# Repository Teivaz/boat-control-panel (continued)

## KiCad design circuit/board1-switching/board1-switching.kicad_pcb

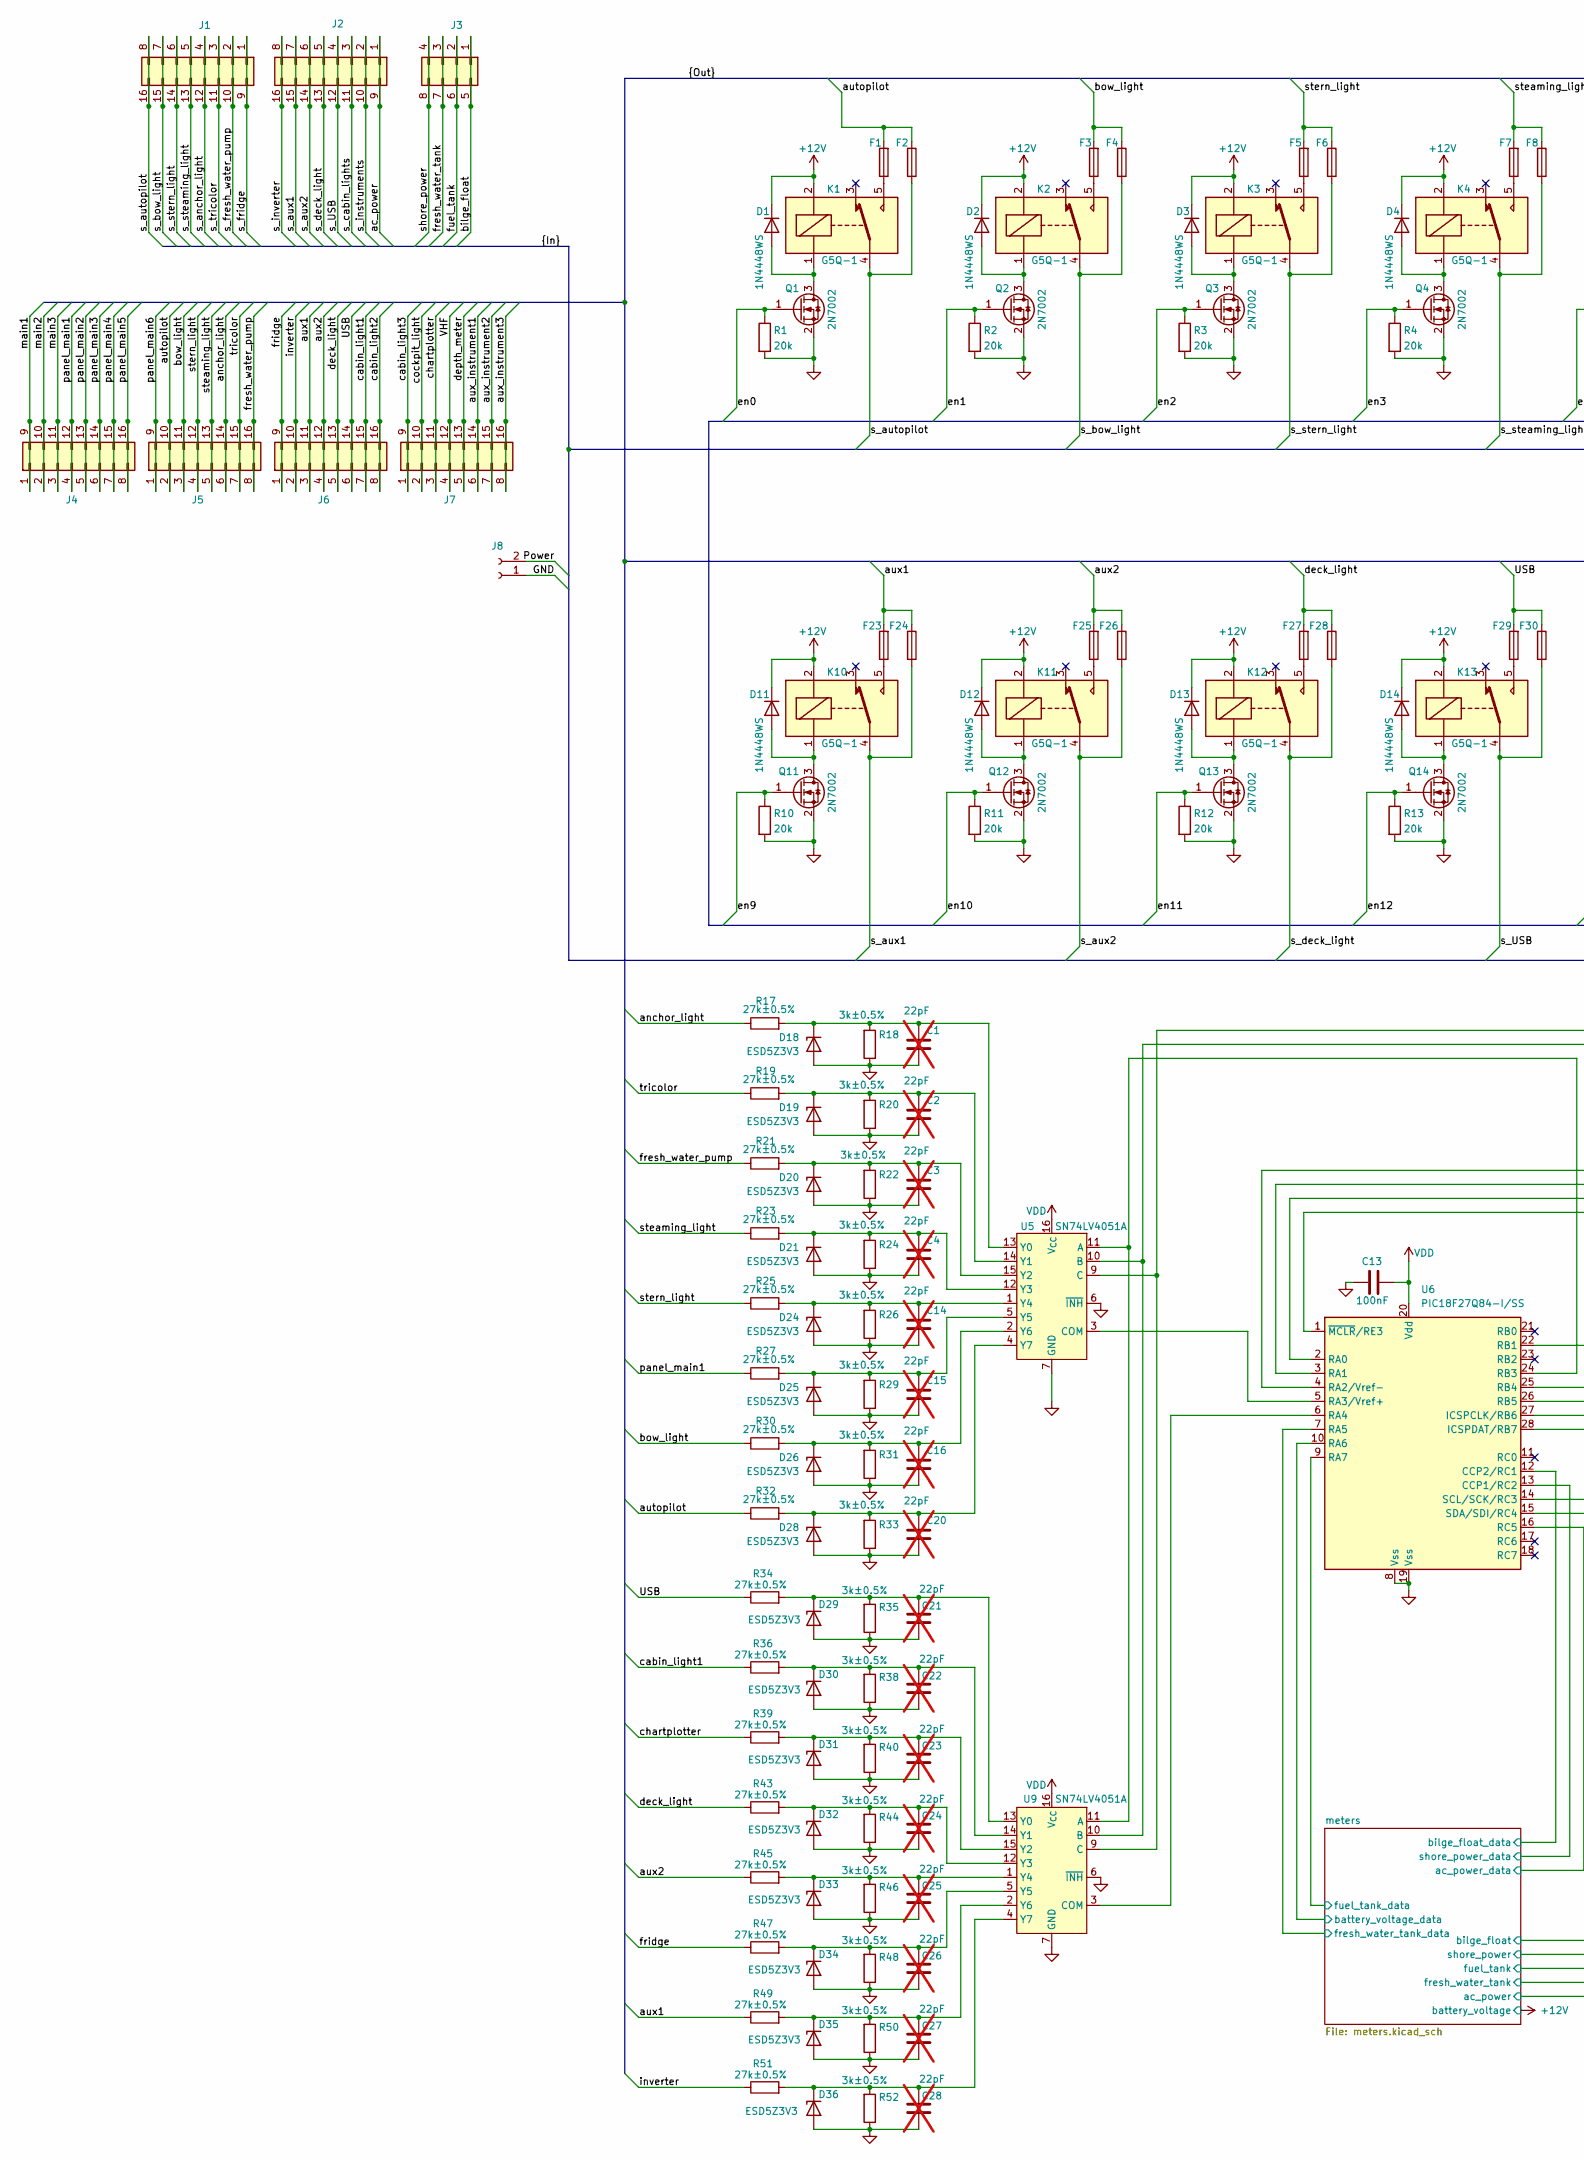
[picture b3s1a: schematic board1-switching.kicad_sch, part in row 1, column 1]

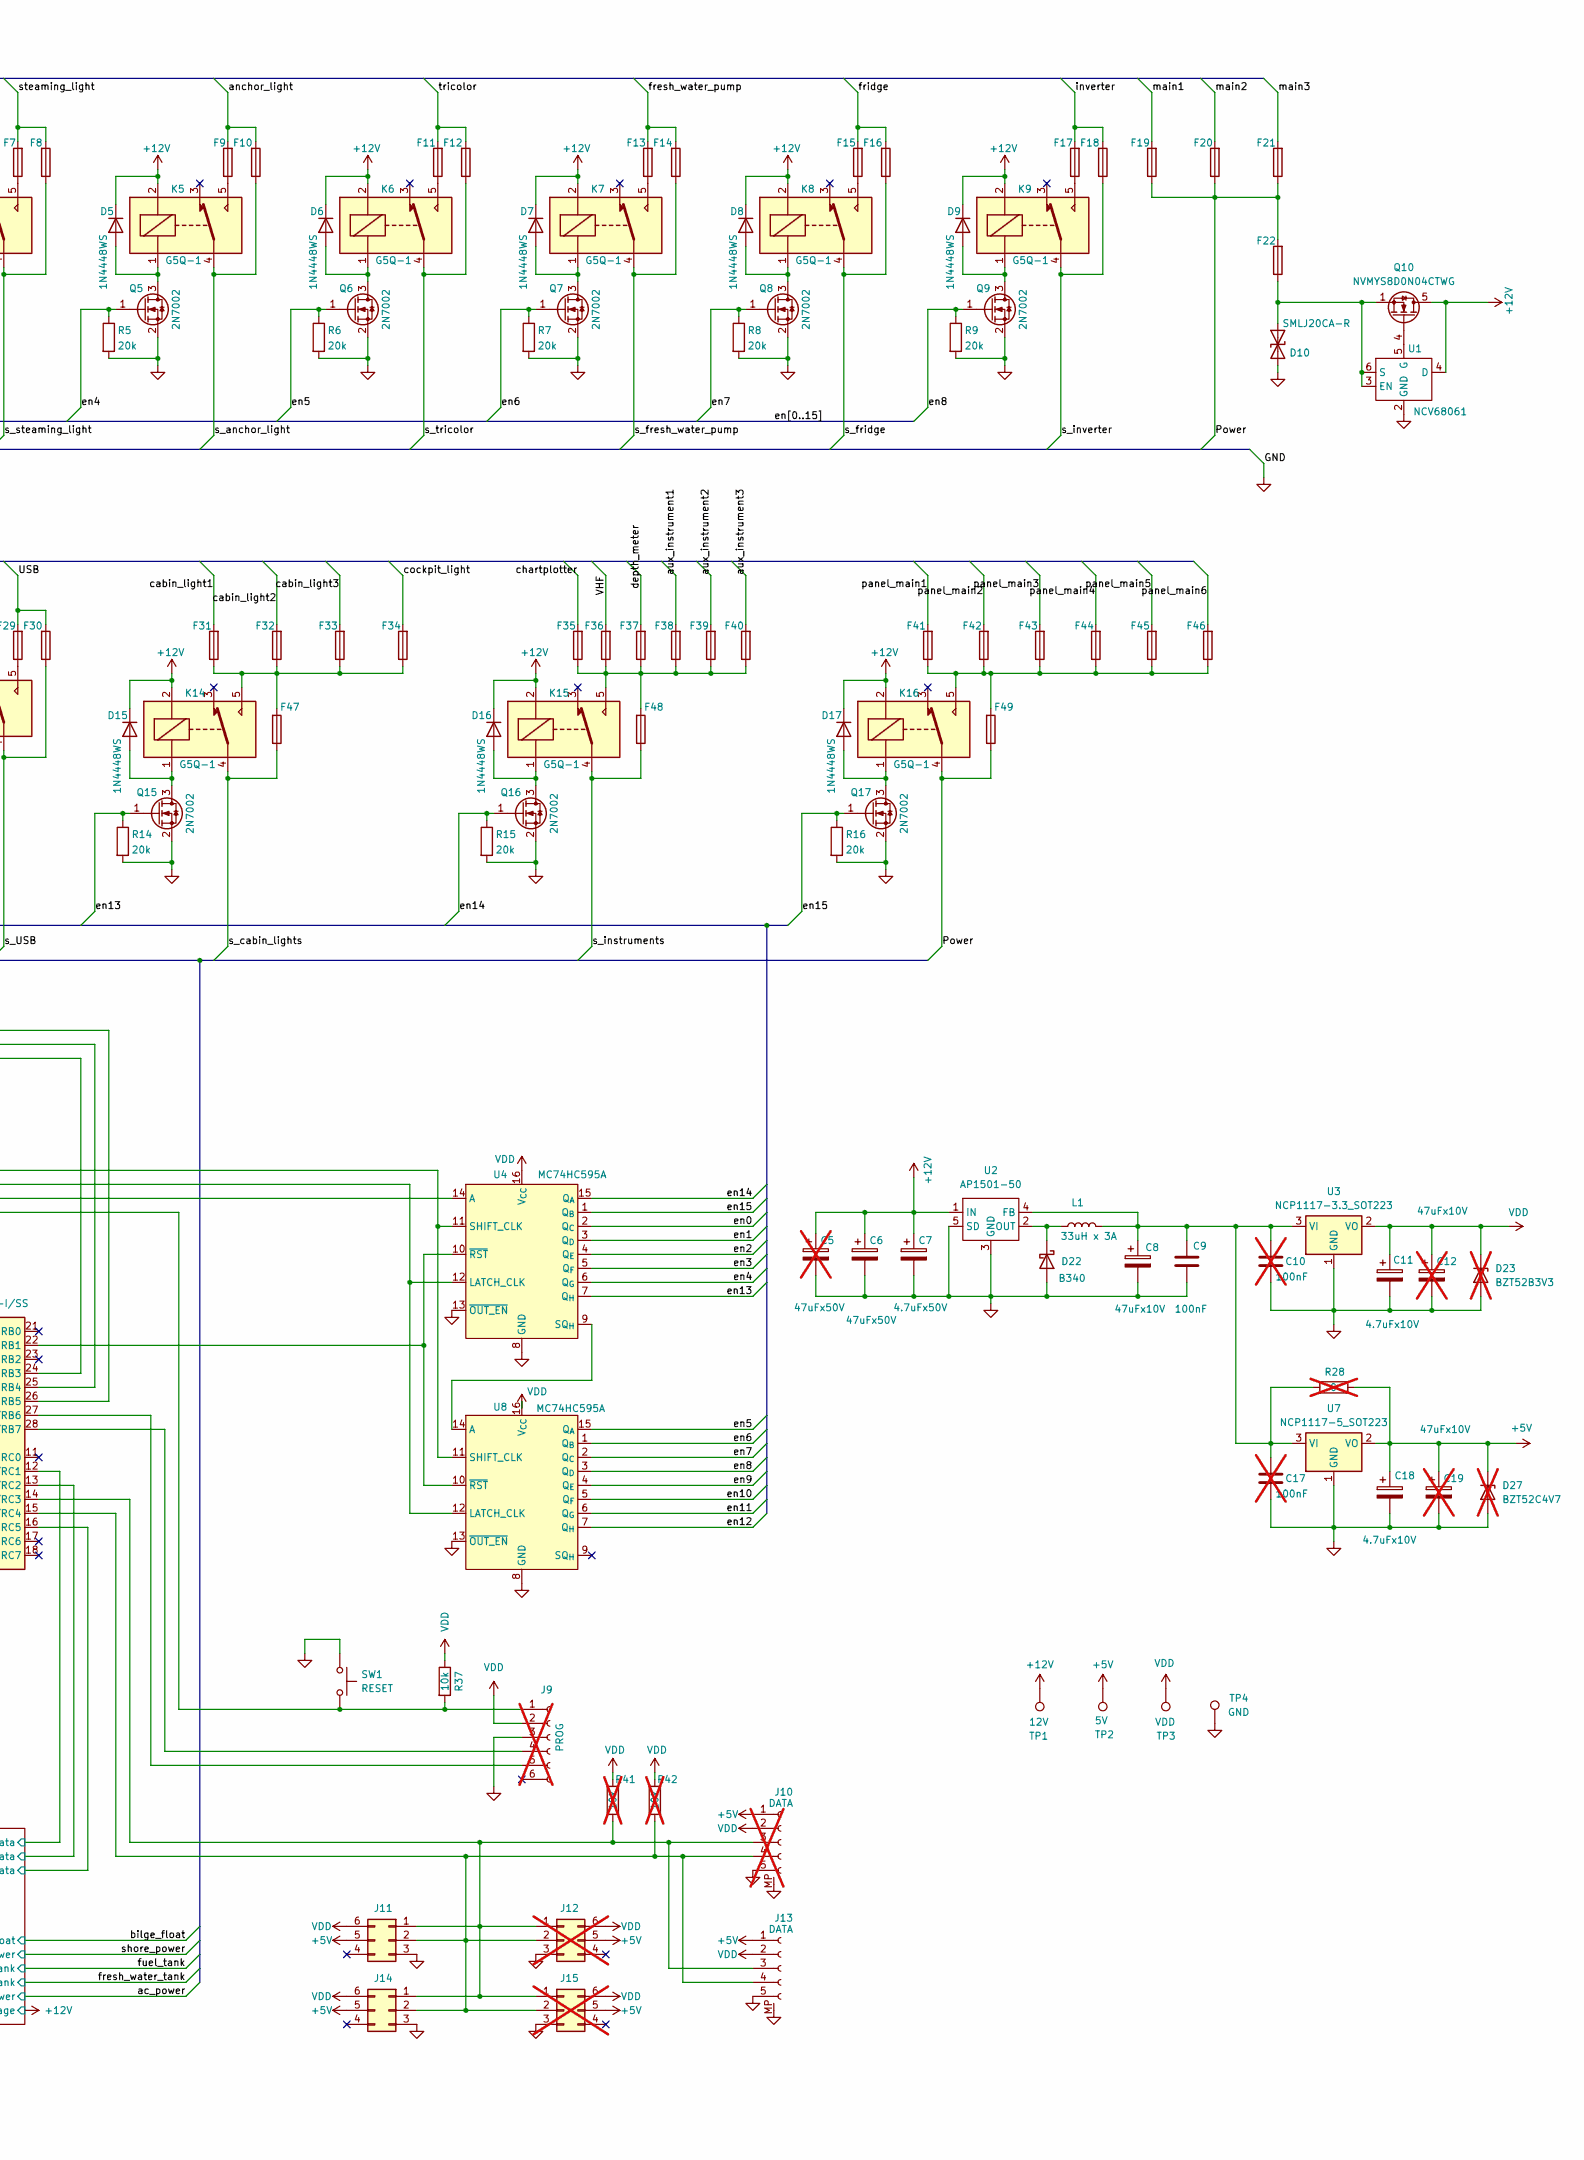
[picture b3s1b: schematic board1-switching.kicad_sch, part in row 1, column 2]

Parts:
C1, C2, C3, C4, C14, C15, C16, C20, C21, C22, C23, C24, C25, C26, C27, C28: 22pF; C_0805_2012Metric_Pad1.18x1.45mm_HandSolder; not fitted
C5: 47uFx50V; CP_Elec_8x6.5; not fitted
C6: 47uFx50V; CP_Elec_8x6.5
C7: 4.7uFx50V; C_Elec_5x5.4
C8: 47uFx10V; CP_EIA-3528-12_Kemet-T_HandSolder
C9, C13: 100nF; C_0805_2012Metric_Pad1.18x1.45mm_HandSolder
C10, C17: 100nF; C_0805_2012Metric_Pad1.18x1.45mm_HandSolder; not fitted
C11, C18: 4.7uFx10V; CP_EIA-3216-10_Kemet-I_HandSolder
C12, C19: 47uFx10V; CP_EIA-3528-12_Kemet-T_HandSolder; not fitted
D1, D2, D3, D4, D5, D6, D7, D8, D9, D11, D12, D13, D14, D15, D16, D17: 1N4448WS; D_SOD-323_HandSoldering
D10: SMLJ20CA-R; D_SMC
D18, D19, D20, D21, D24, D25, D26, D28, D29, D30, D31, D32, D33, D34, D35, D36: ESD5Z3V3; D_SOD-523
D22: B340; D_B340-SMAF
D23: BZT52B3V3; D_SOD-123F; not fitted
D27: BZT52C4V7; D_SOD-123F; not fitted
F1, F2, F3, F4, F5, F6, F7, F8, F9, F10, F11, F12, F13, F14, F15, F16, F17, F18, F19, F20, F21, F22, F23, F24, F25, F26, F27, F28, F29, F30, F31, F32, F33, F34, F35, F36, F37, F38, F39, F40, F41, F42, F43, F44, F45, F46, F47, F48, F49: Fuse-Keystone-3557-2
J1, J2, J4, J5, J6, J7: Con_2x08_Amphenol-QT08CDP
J3: Con_2x04_Amphenol-QT04CDP
J8: J_Molex_38710-6302
J9: PinHeader_1x06_P2.54mm_Vertical; not fitted
J10: Molex_Pico-Lock_504050-0591_1x05-1MP_P1.50mm_Horizontal; not fitted
J11, J14: Conn_02x03_Counter_Clockwise; Con-Amphenol-76385-303LF
J12, J15: Conn_02x03_Counter_Clockwise; Con-Amphenol-76385-303LF; not fitted
J13: Molex_Pico-Lock_504050-0591_1x05-1MP_P1.50mm_Horizontal
K1, K2, K3, K4, K5, K6, K7, K8, K9, K10, K11, K12, K13, K14, K15, K16: G5Q-1; Relay-TE-V23086-C1xxx
L1: 33uH x 3A; L_Abracon_AMDLA1004S-330MT
Q1, Q2, Q3, Q4, Q5, Q6, Q7, Q8, Q9, Q11, Q12, Q13, Q14, Q15, Q16, Q17: 2N7002; SOT-23
Q10: NVMYS8D0N04CTWG; LFPAK4_4.90x4.15x1.15MM_1.27P
R1, R2, R3, R4, R5, R6, R7, R8, R9, R10, R11, R12, R13, R14, R15, R16: 20k; R_0805_2012Metric_Pad1.20x1.40mm_HandSolder
R17, R19, R21, R23, R25, R27, R30, R32, R34, R36, R39, R43, R45, R47, R49, R51: 27k±0.5%; R_0805_2012Metric_Pad1.20x1.40mm_HandSolder
R18, R20, R22, R24, R26, R29, R31, R33, R35, R38, R40, R44, R46, R48, R50, R52: 3k±0.5%; R_0805_2012Metric_Pad1.20x1.40mm_HandSolder
R28: 0; R_0805_2012Metric_Pad1.20x1.40mm_HandSolder; not fitted
R37: 10k; R_0805_2012Metric_Pad1.20x1.40mm_HandSolder
R41, R42: 10k; R_0805_2012Metric_Pad1.20x1.40mm_HandSolder; not fitted
SW1: RESET; ButtonSMT_CnK_KSC2_J
TP1: 12V; TestPoint_Pad_D2.0mm
TP2: 5V; TestPoint_Pad_D2.0mm
TP3: VDD; TestPoint_Pad_D2.0mm
TP4: GND; TestPoint_Pad_D2.0mm
U1: NCV68061; TSOP-6_3.00x1.5x0.90mm_P0.95mm
U2: AP1501-50; TO-263-5_TabPin3
U3: NCP1117-3.3_SOT223; SOT-223-3_TabPin2
U4, U8: MC74HC595A; SOIC-16_3.9x9.9mm_P1.27mm
U5, U9: SN74LV4051A; SOIC-16_3.9x9.9mm_P1.27mm
U6: PIC18F27Q84-I/SS; SSOP-28-5.3mm
U7: NCP1117-5_SOT223; SOT-223-3_TabPin2

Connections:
+5V: C18.1, C19.1, D27.1 (K), J10.1, J11.5, J12.5, J13.1, J14.5, J15.5, R28.1, TP2.1, U7.2 (VO); also elsewhere on the board
+12V: C5.1, C6.1, C7.1, D1.1 (K), D2.1 (K), D3.1 (K), D4.1 (K), D5.1 (K), D6.1 (K), D7.1 (K), D8.1 (K), D9.1 (K), D11.1 (K), D12.1 (K), D13.1 (K), D14.1 (K), D15.1 (K), D16.1 (K), D17.1 (K), K1.2, K2.2, K3.2, K4.2, K5.2, K6.2, K7.2, K8.2, K9.2, K10.2, K11.2, K12.2, K13.2, K14.2, K15.2, K16.2, Q10.5 (D), TP1.1, U1.4 (D), U2.1 (IN); also elsewhere on the board
/Power: F19.1, F19.2, F20.1, F20.2, F21.1, F21.2, F22.3, F22.4, F49.1, F49.2, J8.2, K16.4
/USB: F29.3, F29.4, F30.3, F30.4, J6.6, J6.14, R34.1
/VHF: F36.3, F36.4, J7.4, J7.12
/ac_power: J2.1, J2.9; also elsewhere on the board
/anchor_light: F9.3, F9.4, F10.3, F10.4, J5.6, J5.14, R17.1
/autopilot: F1.3, F1.4, F2.3, F2.4, J5.2, J5.10, R32.1
/aux1: F23.3, F23.4, F24.3, F24.4, J6.3, J6.11, R49.1
/aux2: F25.3, F25.4, F26.3, F26.4, J6.4, J6.12, R45.1
/aux_instrument1: F38.3, F38.4, J7.6, J7.14
/aux_instrument2: F39.3, F39.4, J7.7, J7.15
/aux_instrument3: F40.3, F40.4, J7.8, J7.16
/bilge_float: J3.1, J3.5; also elsewhere on the board
/bow_light: F3.3, F3.4, F4.3, F4.4, J5.3, J5.11, R30.1
/cabin_light1: F31.3, F31.4, J6.7, J6.15, R36.1
/cabin_light2: F32.3, F32.4, J6.8, J6.16
/cabin_light3: F33.3, F33.4, J7.1, J7.9
/chartplotter: F35.3, F35.4, J7.3, J7.11, R39.1
/cockpit_light: F34.3, F34.4, J7.2, J7.10
/deck_light: F27.3, F27.4, F28.3, F28.4, J6.5, J6.13, R43.1
/depth_meter: F37.3, F37.4, J7.5, J7.13
/en0: Q1.1 (G), R1.1, U4.2 (Q_{C})
/en1: Q2.1 (G), R2.1, U4.3 (Q_{D})
/en2: Q3.1 (G), R3.1, U4.4 (Q_{E})
/en3: Q4.1 (G), R4.1, U4.5 (Q_{F})
/en4: Q5.1 (G), R5.1, U4.6 (Q_{G})
/en5: Q6.1 (G), R6.1, U8.15 (Q_{A})
/en6: Q7.1 (G), R7.1, U8.1 (Q_{B})
/en7: Q8.1 (G), R8.1, U8.2 (Q_{C})
/en8: Q9.1 (G), R9.1, U8.3 (Q_{D})
/en9: Q11.1 (G), R10.1, U8.4 (Q_{E})
/en10: Q12.1 (G), R11.1, U8.5 (Q_{F})
/en11: Q13.1 (G), R12.1, U8.6 (Q_{G})
/en12: Q14.1 (G), R13.1, U8.7 (Q_{H})
/en13: Q15.1 (G), R14.1, U4.7 (Q_{H})
/en14: Q16.1 (G), R15.1, U4.15 (Q_{A})
/en15: Q17.1 (G), R16.1, U4.1 (Q_{B})
/fresh_water_pump: F13.3, F13.4, F14.3, F14.4, J5.8, J5.16, R21.1
/fresh_water_tank: J3.3, J3.7; also elsewhere on the board
/fridge: F15.3, F15.4, F16.3, F16.4, J6.1, J6.9, R47.1
/fuel_tank: J3.2, J3.6; also elsewhere on the board
/inverter: F17.3, F17.4, F18.3, F18.4, J6.2, J6.10, R51.1
/main1: F19.3, F19.4, J4.1, J4.9
/main2: F20.3, F20.4, J4.2, J4.10
/main3: F21.3, F21.4, J4.3, J4.11
/meters/ac_power_data: U6.16 (RC5); also elsewhere on the board
/meters/battery_voltage_data: U6.10 (RA6); also elsewhere on the board
/meters/bilge_float_data: U6.12 (CCP2/RC1); also elsewhere on the board
/meters/fresh_water_tank_data: U6.7 (RA5); also elsewhere on the board
/meters/fuel_tank_data: U6.9 (RA7); also elsewhere on the board
/meters/shore_power_data: U6.13 (CCP1/RC2); also elsewhere on the board
/panel_main1: F41.3, F41.4, J4.4, J4.12, R27.1
/panel_main2: F42.3, F42.4, J4.5, J4.13
/panel_main3: F43.3, F43.4, J4.6, J4.14
/panel_main4: F44.3, F44.4, J4.7, J4.15
/panel_main5: F45.3, F45.4, J4.8, J4.16
/panel_main6: F46.3, F46.4, J5.1, J5.9
/s_USB: F30.1, F30.2, J2.4, J2.12, K13.4
/s_anchor_light: F10.1, F10.2, J1.4, J1.12, K5.4
/s_autopilot: F2.1, F2.2, J1.8, J1.16, K1.4
/s_aux1: F24.1, F24.2, J2.7, J2.15, K10.4
/s_aux2: F26.1, F26.2, J2.6, J2.14, K11.4
/s_bow_light: F4.1, F4.2, J1.7, J1.15, K2.4
/s_cabin_lights: F47.1, F47.2, J2.3, J2.11, K14.4
/s_deck_light: F28.1, F28.2, J2.5, J2.13, K12.4
/s_fresh_water_pump: F14.1, F14.2, J1.2, J1.10, K7.4
/s_fridge: F16.1, F16.2, J1.1, J1.9, K8.4
/s_instruments: F48.1, F48.2, J2.2, J2.10, K15.4
/s_inverter: F18.1, F18.2, J2.8, J2.16, K9.4
/s_steaming_light: F8.1, F8.2, J1.5, J1.13, K4.4
/s_stern_light: F6.1, F6.2, J1.6, J1.14, K3.4
/s_tricolor: F12.1, F12.2, J1.3, J1.11, K6.4
/shore_power: J3.4, J3.8; also elsewhere on the board
/steaming_light: F7.3, F7.4, F8.3, F8.4, J5.5, J5.13, R23.1
/stern_light: F5.3, F5.4, F6.3, F6.4, J5.4, J5.12, R25.1
/tricolor: F11.3, F11.4, F12.3, F12.4, J5.7, J5.15, R19.1
GND: C1.1, C2.1, C3.1, C4.1, C5.2, C6.2, C7.2, C8.2, C9.2, C10.2, C11.2, C12.2, C13.2, C14.1, C15.1, C16.1, C17.2, C18.2, C19.2, C20.1, C21.1, C22.1, C23.1, C24.1, C25.1, C26.1, C27.1, C28.1, D10.2 (A2), D18.2 (A), D19.2 (A), D20.2 (A), D21.2 (A), D22.2 (A), D23.2 (A), D24.2 (A), D25.2 (A), D26.2 (A), D27.2 (A), D28.2 (A), D29.2 (A), D30.2 (A), D31.2 (A), D32.2 (A), D33.2 (A), D34.2 (A), D35.2 (A), D36.2 (A), J8.1, J9.3, J10.5, J10.MP, J11.3, J12.3, J13.5, J13.MP, J14.3, J15.3, Q1.2 (S), Q2.2 (S), Q3.2 (S), Q4.2 (S), Q5.2 (S), Q6.2 (S), Q7.2 (S), Q8.2 (S), Q9.2 (S), Q11.2 (S), Q12.2 (S), Q13.2 (S), Q14.2 (S), Q15.2 (S), Q16.2 (S), Q17.2 (S), R1.2, R2.2, R3.2, R4.2, R5.2, R6.2, R7.2, R8.2, R9.2, R10.2, R11.2, R12.2, R13.2, R14.2, R15.2, R16.2, R18.1, R20.1, R22.1, R24.1, R26.1, R29.1, R31.1, R33.1, R35.1, R38.1, R40.1, R44.1, R46.1, R48.1, R50.1, R52.1, SW1.1, SW1.3, TP4.1, U1.2 (GND), U2.3 (GND), U2.5 (SD), U3.1 (GND), U4.8 (GND), U4.13 (~OUT_EN), U5.6 (~INH), U5.7 (GND), U5.8 (GND), U6.8 (Vss), U6.19 (Vss), U7.1 (GND), U8.8 (GND), U8.13 (~OUT_EN), U9.6 (~INH), U9.7 (GND), U9.8 (GND); also elsewhere on the board
unnamed: D1.2 (A), K1.1, Q1.3 (D)
unnamed: D2.2 (A), K2.1, Q2.3 (D)
unnamed: D3.2 (A), K3.1, Q3.3 (D)
unnamed: D4.2 (A), K4.1, Q4.3 (D)
unnamed: D5.2 (A), K5.1, Q5.3 (D)
unnamed: D6.2 (A), K6.1, Q6.3 (D)
unnamed: D7.2 (A), K7.1, Q7.3 (D)
unnamed: D8.2 (A), K8.1, Q8.3 (D)
unnamed: D9.2 (A), K9.1, Q9.3 (D)
unnamed: D10.1 (A1), F22.1, F22.2, Q10.1 (S), Q10.2 (S), Q10.3 (S), U1.3 (EN), U1.6 (S)
unnamed: D11.2 (A), K10.1, Q11.3 (D)
unnamed: D12.2 (A), K11.1, Q12.3 (D)
unnamed: D13.2 (A), K12.1, Q13.3 (D)
unnamed: D14.2 (A), K13.1, Q14.3 (D)
unnamed: D15.2 (A), K14.1, Q15.3 (D)
unnamed: D16.2 (A), K15.1, Q16.3 (D)
unnamed: D17.2 (A), K16.1, Q17.3 (D)
unnamed: C1.2, D18.1 (K), R17.2, R18.2, U5.13 (Y0)
unnamed: C2.2, D19.1 (K), R19.2, R20.2, U5.14 (Y1)
unnamed: C3.2, D20.1 (K), R21.2, R22.2, U5.15 (Y2)
unnamed: C4.2, D21.1 (K), R23.2, R24.2, U5.12 (Y3)
unnamed: D22.1 (K), L1.1, U2.2 (OUT)
unnamed: C14.2, D24.1 (K), R25.2, R26.2, U5.1 (Y4)
unnamed: C15.2, D25.1 (K), R27.2, R29.2, U5.5 (Y5)
unnamed: C16.2, D26.1 (K), R30.2, R31.2, U5.2 (Y6)
unnamed: C20.2, D28.1 (K), R32.2, R33.2, U5.4 (Y7)
unnamed: C21.2, D29.1 (K), R34.2, R35.2, U9.13 (Y0)
unnamed: C22.2, D30.1 (K), R36.2, R38.2, U9.14 (Y1)
unnamed: C23.2, D31.1 (K), R39.2, R40.2, U9.15 (Y2)
unnamed: C24.2, D32.1 (K), R43.2, R44.2, U9.12 (Y3)
unnamed: C25.2, D33.1 (K), R45.2, R46.2, U9.1 (Y4)
unnamed: C26.2, D34.1 (K), R47.2, R48.2, U9.5 (Y5)
unnamed: C27.2, D35.1 (K), R49.2, R50.2, U9.2 (Y6)
unnamed: C28.2, D36.1 (K), R51.2, R52.2, U9.4 (Y7)
unnamed: F1.1, F1.2, K1.5
unnamed: F3.1, F3.2, K2.5
unnamed: F5.1, F5.2, K3.5
unnamed: F7.1, F7.2, K4.5
unnamed: F9.1, F9.2, K5.5
unnamed: F11.1, F11.2, K6.5
unnamed: F13.1, F13.2, K7.5
unnamed: F15.1, F15.2, K8.5
unnamed: F17.1, F17.2, K9.5
unnamed: F23.1, F23.2, K10.5
unnamed: F25.1, F25.2, K11.5
unnamed: F27.1, F27.2, K12.5
unnamed: F29.1, F29.2, K13.5
unnamed: F31.1, F31.2, F32.1, F32.2, F33.1, F33.2, F34.1, F34.2, F47.3, F47.4, K14.5
unnamed: F35.1, F35.2, F36.1, F36.2, F37.1, F37.2, F38.1, F38.2, F39.1, F39.2, F40.1, F40.2, F48.3, F48.4, K15.5
unnamed: F41.1, F41.2, F42.1, F42.2, F43.1, F43.2, F44.1, F44.2, F45.1, F45.2, F46.1, F46.2, F49.3, F49.4, K16.5
unnamed: J9.1, R37.2, SW1.2, SW1.4, U6.1 (~MCLR/RE3)
unnamed: J9.4, U6.28 (ICSPDAT/RB7)
unnamed: J9.5, U6.27 (ICSPCLK/RB6)
unnamed: J10.3, J11.1, J12.1, J13.3, J14.1, J15.1, R41.2, U6.14 (SCL/SCK/RC3)
unnamed: J10.4, J11.2, J12.2, J13.4, J14.2, J15.2, R42.2, U6.15 (SDA/SDI/RC4)
unnamed: Q10.4 (G), U1.5 (G)
unnamed: C8.1, C9.1, C10.1, C17.1, L1.2, R28.2, U2.4 (FB), U3.3 (VI), U7.3 (VI)
unnamed: U4.14 (A), U6.2 (RA0)
unnamed: U4.12 (LATCH_CLK), U6.3 (RA1), U8.12 (LATCH_CLK)
unnamed: U4.11 (SHIFT_CLK), U6.4 (RA2/Vref-), U8.11 (SHIFT_CLK)
unnamed: U4.9 (SQ_{H}), U8.14 (A)
unnamed: U4.10 (~RST), U6.22 (RB1), U8.10 (~RST)
unnamed: U5.11 (A), U6.24 (RB3), U9.11 (A)
unnamed: U5.10 (B), U6.25 (RB4), U9.10 (B)
unnamed: U5.9 (C), U6.26 (RB5), U9.9 (C)
unnamed: U5.3 (COM), U6.5 (RA3/Vref+)
unnamed: U6.6 (RA4), U9.3 (COM)
VDD: C11.1, C12.1, C13.1, D23.1 (K), J9.2, J10.2, J11.6, J12.6, J13.2, J14.6, J15.6, R37.1, R41.1, R42.1, TP3.1, U3.2 (VO), U4.16 (V_{CC}), U5.16 (V_{CC}), U6.20 (Vdd), U8.16 (V_{CC}), U9.16 (V_{CC}); also elsewhere on the board

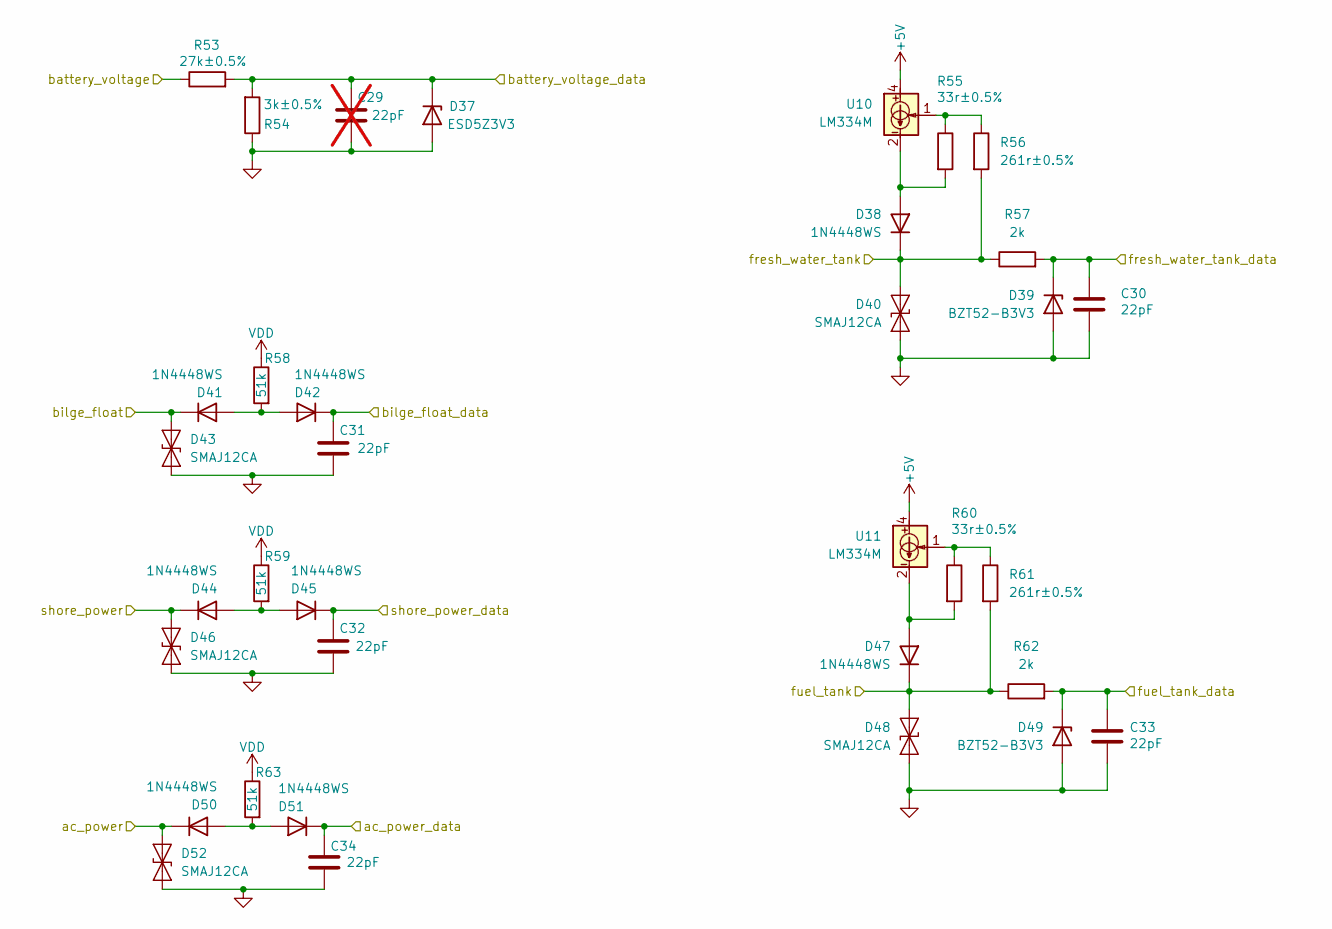
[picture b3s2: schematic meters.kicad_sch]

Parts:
C29: 22pF; C_0805_2012Metric_Pad1.18x1.45mm_HandSolder; not fitted
C30, C31, C32, C33, C34: 22pF; C_0805_2012Metric_Pad1.18x1.45mm_HandSolder
D37: ESD5Z3V3; D_SOD-523
D38, D41, D42, D44, D45, D47, D50, D51: 1N4448WS; D_SOD-323_HandSoldering
D39, D49: BZT52-B3V3; D_SOD-123
D40, D43, D46, D48, D52: SMAJ12CA; D_SMA
R53: 27k±0.5%; R_0805_2012Metric_Pad1.20x1.40mm_HandSolder
R54: 3k±0.5%; R_0805_2012Metric_Pad1.20x1.40mm_HandSolder
R55, R60: 33r±0.5%; R_0805_2012Metric_Pad1.20x1.40mm_HandSolder
R56, R61: 261r±0.5%; R_0805_2012Metric_Pad1.20x1.40mm_HandSolder
R57, R62: 2k; R_0805_2012Metric_Pad1.20x1.40mm_HandSolder
R58, R59, R63: 51k; R_0805_2012Metric_Pad1.20x1.40mm_HandSolder
U10, U11: LM334M; SOIC-8_3.9x4.9mm_P1.27mm

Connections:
+5V: U10.4, U11.4; also elsewhere on the board
+12V: R53.1; also elsewhere on the board
/ac_power: D50.1 (K), D52.2 (A2); also elsewhere on the board
/bilge_float: D41.1 (K), D43.2 (A2); also elsewhere on the board
/fresh_water_tank: D38.1 (K), D40.2 (A2), R56.2, R57.1; also elsewhere on the board
/fuel_tank: D47.1 (K), D48.2 (A2), R61.2, R62.1; also elsewhere on the board
/meters/ac_power_data: C34.1, D51.1 (K); also elsewhere on the board
/meters/battery_voltage_data: C29.2, D37.1 (K), R53.2, R54.2; also elsewhere on the board
/meters/bilge_float_data: C31.1, D42.1 (K); also elsewhere on the board
/meters/fresh_water_tank_data: C30.1, D39.1 (K), R57.2; also elsewhere on the board
/meters/fuel_tank_data: C33.1, D49.1 (K), R62.2; also elsewhere on the board
/meters/shore_power_data: C32.1, D45.1 (K); also elsewhere on the board
/shore_power: D44.1 (K), D46.2 (A2); also elsewhere on the board
GND: C29.1, C30.2, C31.2, C32.2, C33.2, C34.2, D37.2 (A), D39.2 (A), D40.1 (A1), D43.1 (A1), D46.1 (A1), D48.1 (A1), D49.2 (A), D52.1 (A1), R54.1; also elsewhere on the board
unnamed: D38.2 (A), R55.2, U10.2, U10.3, U10.6, U10.7
unnamed: D41.2 (A), D42.2 (A), R58.2
unnamed: D44.2 (A), D45.2 (A), R59.2
unnamed: D47.2 (A), R60.2, U11.2, U11.3, U11.6, U11.7
unnamed: D50.2 (A), D51.2 (A), R63.2
unnamed: R55.1, R56.1, U10.1
unnamed: R60.1, R61.1, U11.1
VDD: R58.1, R59.1, R63.1; also elsewhere on the board

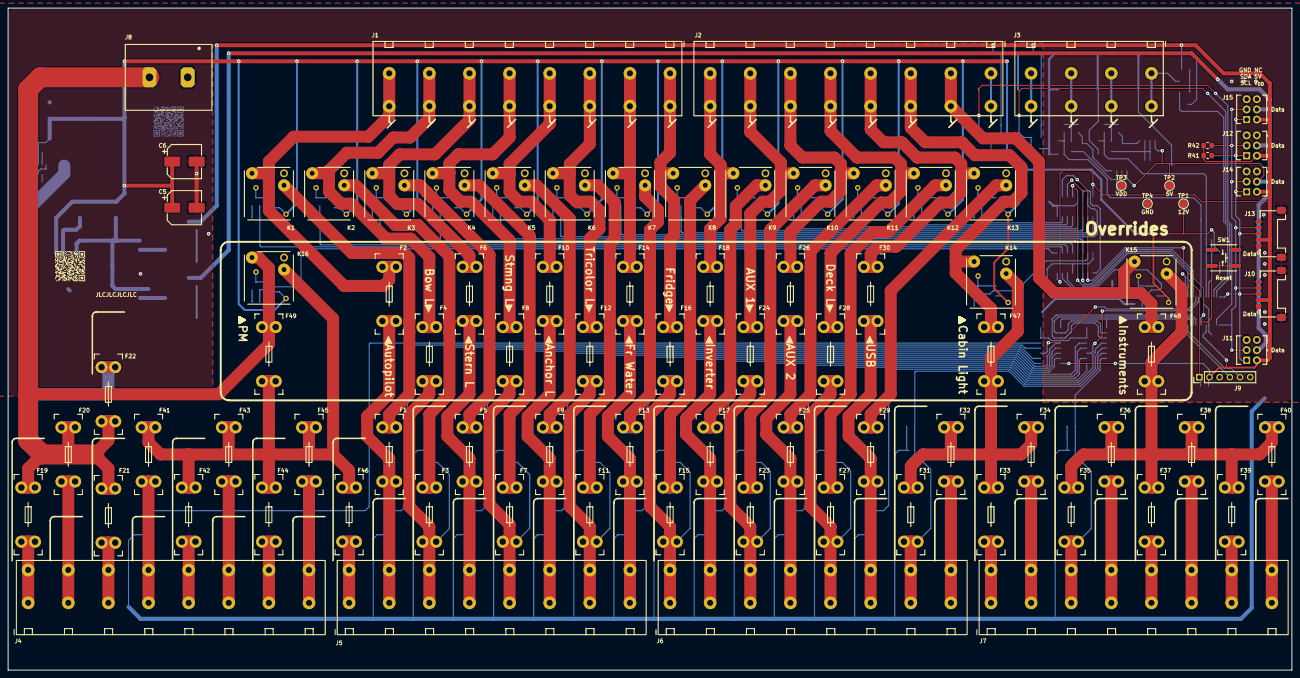
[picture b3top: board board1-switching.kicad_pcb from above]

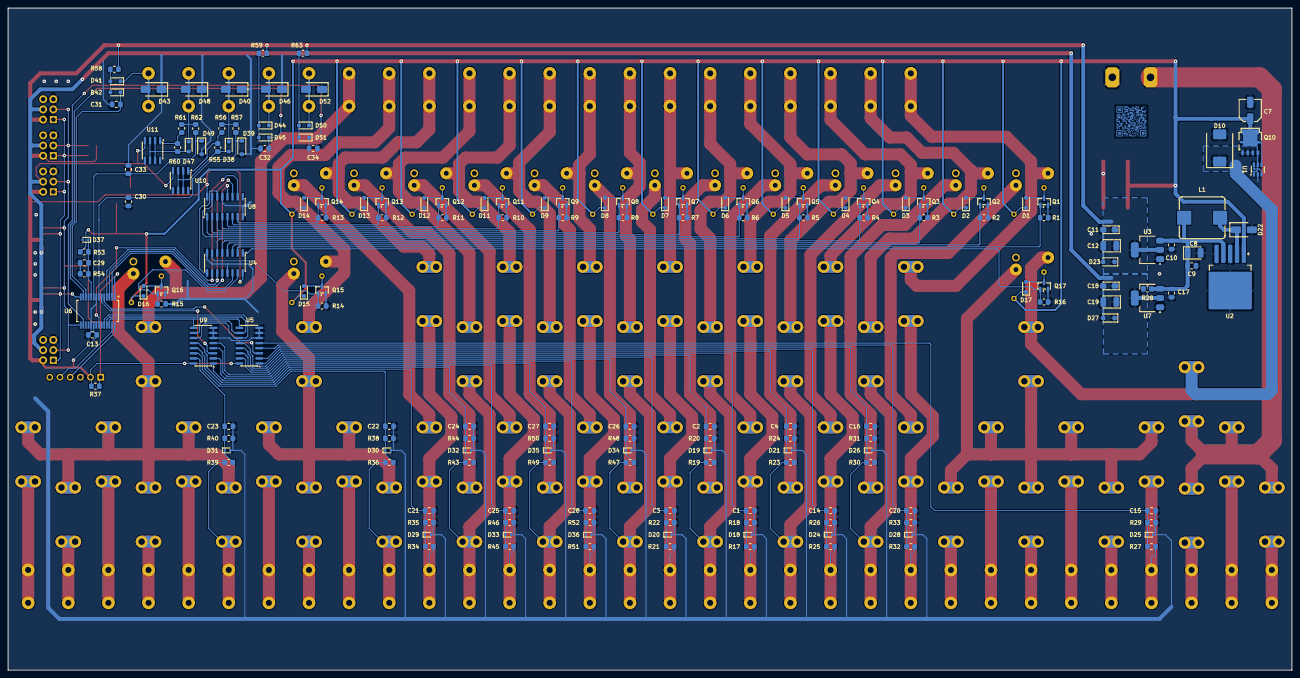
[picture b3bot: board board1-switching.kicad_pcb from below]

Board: 2 copper layers, 320.0 x 165.0 mm, 263 parts (174 on the bottom side), 153 nets.
